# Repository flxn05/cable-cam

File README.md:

# Cable Cam

Lightweight Cable-Cam built with an ESP32, a [cheap chinese motor driver](https://de.aliexpress.com/item/1005006570513212.html?spm=a2g0o.productlist.main.1.5547KPsOKPsOLx&algo_pvid=7422817a-918c-4eda-9140-1a195e1be43c&utparam-url=scene%3Asearch%7Cquery_from%3A) and a power drill motor.

## Showcase

## Parts

- [Motor Driver](https://de.aliexpress.com/item/1005006570513212.html?spm=a2g0o.productlist.main.1.5547KPsOKPsOLx&algo_pvid=7422817a-918c-4eda-9140-1a195e1be43c&utparam-url=scene%3Asearch%7Cquery_from%3A) (AliExpress)

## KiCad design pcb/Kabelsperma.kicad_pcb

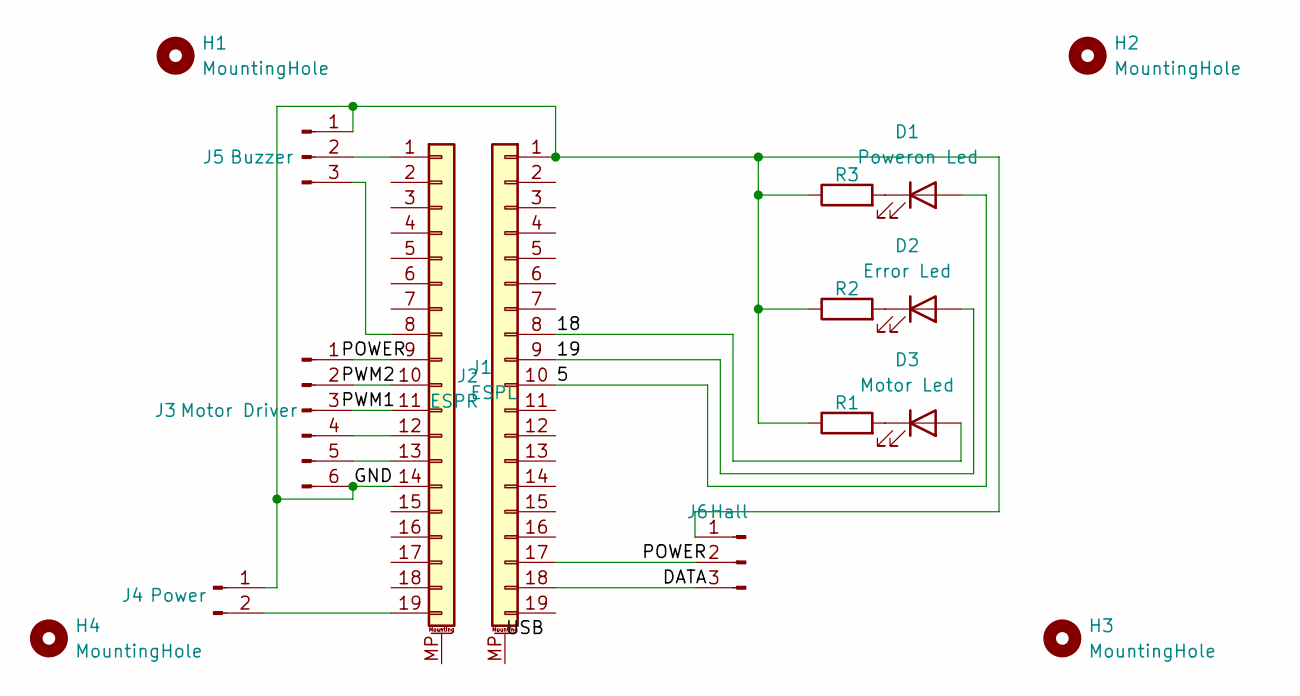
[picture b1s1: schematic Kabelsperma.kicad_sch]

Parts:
D1: Poweron Led; LED_0805_2012Metric_Pad1.15x1.40mm_HandSolder
D2: Error Led; LED_0805_2012Metric_Pad1.15x1.40mm_HandSolder
D3: Motor Led; LED_0805_2012Metric_Pad1.15x1.40mm_HandSolder
H1, H2, H3, H4: MountingHole; MountingHole_2.5mm
J1: ESPL; PinHeader_1x19_P2.54mm_Vertical
J2: ESPR; PinHeader_1x19_P2.54mm_Vertical
J3: Motor Driver; PinHeader_1x06_P2.54mm_Vertical
J4: Power; PinHeader_1x02_P2.54mm_Vertical
J5: Buzzer; PinHeader_1x03_P2.54mm_Vertical
J6: Hall; PinHeader_1x03_P2.54mm_Vertical
R1, R2, R3: R; R_0805_2012Metric_Pad1.20x1.40mm_HandSolder

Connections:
/5: D1.2 (A), J2.10
/18: D3.2 (A), J2.8
/19: D2.2 (A), J2.9
/GND: J1.14, J2.1, J3.6, J4.1, J5.1, J6.1, R1.1, R2.1, R3.1
unnamed: D1.1 (K), R3.2
unnamed: D2.1 (K), R2.2
unnamed: D3.1 (K), R1.2
unnamed: J1.1, J5.2
unnamed: J1.8, J5.3
unnamed: J1.9, J3.1
unnamed: J1.10, J3.2
unnamed: J1.11, J3.3
unnamed: J1.12, J3.4
unnamed: J1.13, J3.5
unnamed: J1.19, J4.2
unnamed: J2.17, J6.2
unnamed: J2.18, J6.3

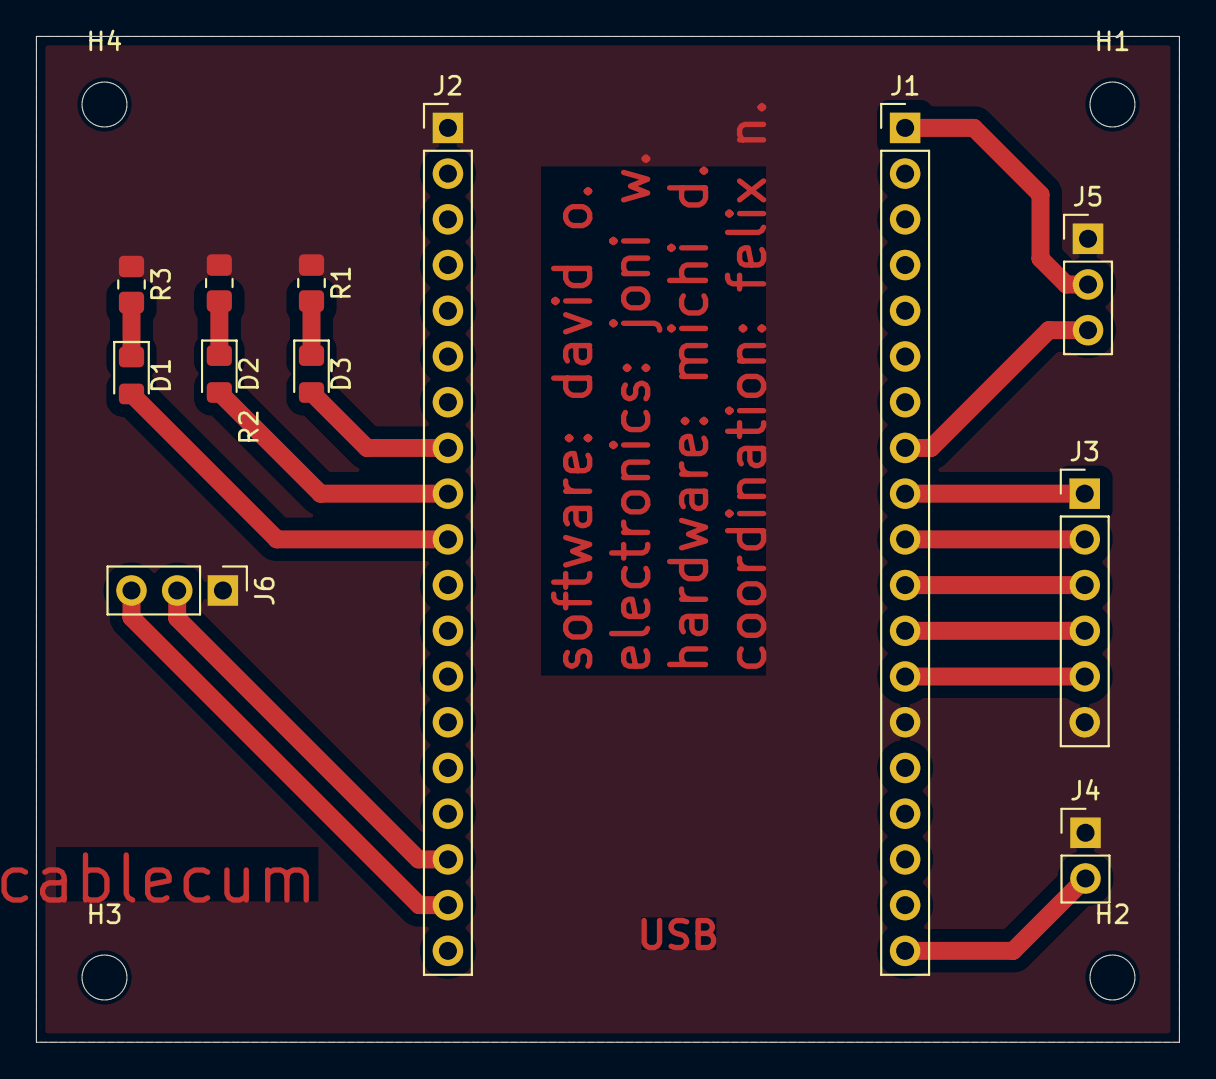
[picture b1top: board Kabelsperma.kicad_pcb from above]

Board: 2 copper layers, 63.5 x 55.9 mm, 16 parts (0 on the bottom side), 17 nets.

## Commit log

2024-06-20 added general description
2024-06-20 added 3d models for the passive wheels; prusa project data
2024-06-20 added motordriver image
2024-06-20 implemented image
2024-10-03 design finished. pls update javascript asap
2024-10-03 design update, psl update js asap
2024-10-03 .current font fix
2024-10-03 body rgb 10 10 10 from 5 5 5
2024-10-03 202020
2024-10-04 removed fullscreen
2024-10-09 Update tesz
2024-10-14 advanced mode
2024-10-14 advanced mode // scrolling enabled
2024-10-14 !important
2024-10-18 Update main1.cpp
    Hooooooooyyyyyyyaaaaaaaaaaa
2024-10-18 dewsign change
2024-10-18 order
2024-10-18 another try
2024-10-19 fixed id errors, added fullscreen function()
2024-10-19 fixed id errors, added fullscreen function(); merged
2024-10-19 fixed id errors, added fullscreen function(); merged styles; min/max values for input elements
2024-10-19 fixed id errors, added fullscreen function(); merged styles; min/max values for input elements; added active effect for input elements and buttons
2024-10-19 onclick
2024-10-20 backup
2024-10-20 Rename main.cpp to main-stable.cpp
2024-10-21 Suiiii
2024-10-21 ll373
2024-10-21 pr btn m -> body
2024-10-21 rem 2nd btn run
2024-10-21 indeximexi.html
2024-10-21 finally fixed ..... (my [chatGPT's]) fault .....
2024-12-01 removed unused lines and added return freset option and replaced alerts with textcontents
2024-12-01 new design, but before continuing, @gerbil008 pls check functionality
2024-12-01 design is ready to deliver
2024-12-01 backup, design and functionality checked, final version
2025-03-10 v1 ipad
2025-03-12 v2 drag ipad
2025-03-12 v2 moveing ipad
2025-03-18 updated 3d models, cnc and pcb
